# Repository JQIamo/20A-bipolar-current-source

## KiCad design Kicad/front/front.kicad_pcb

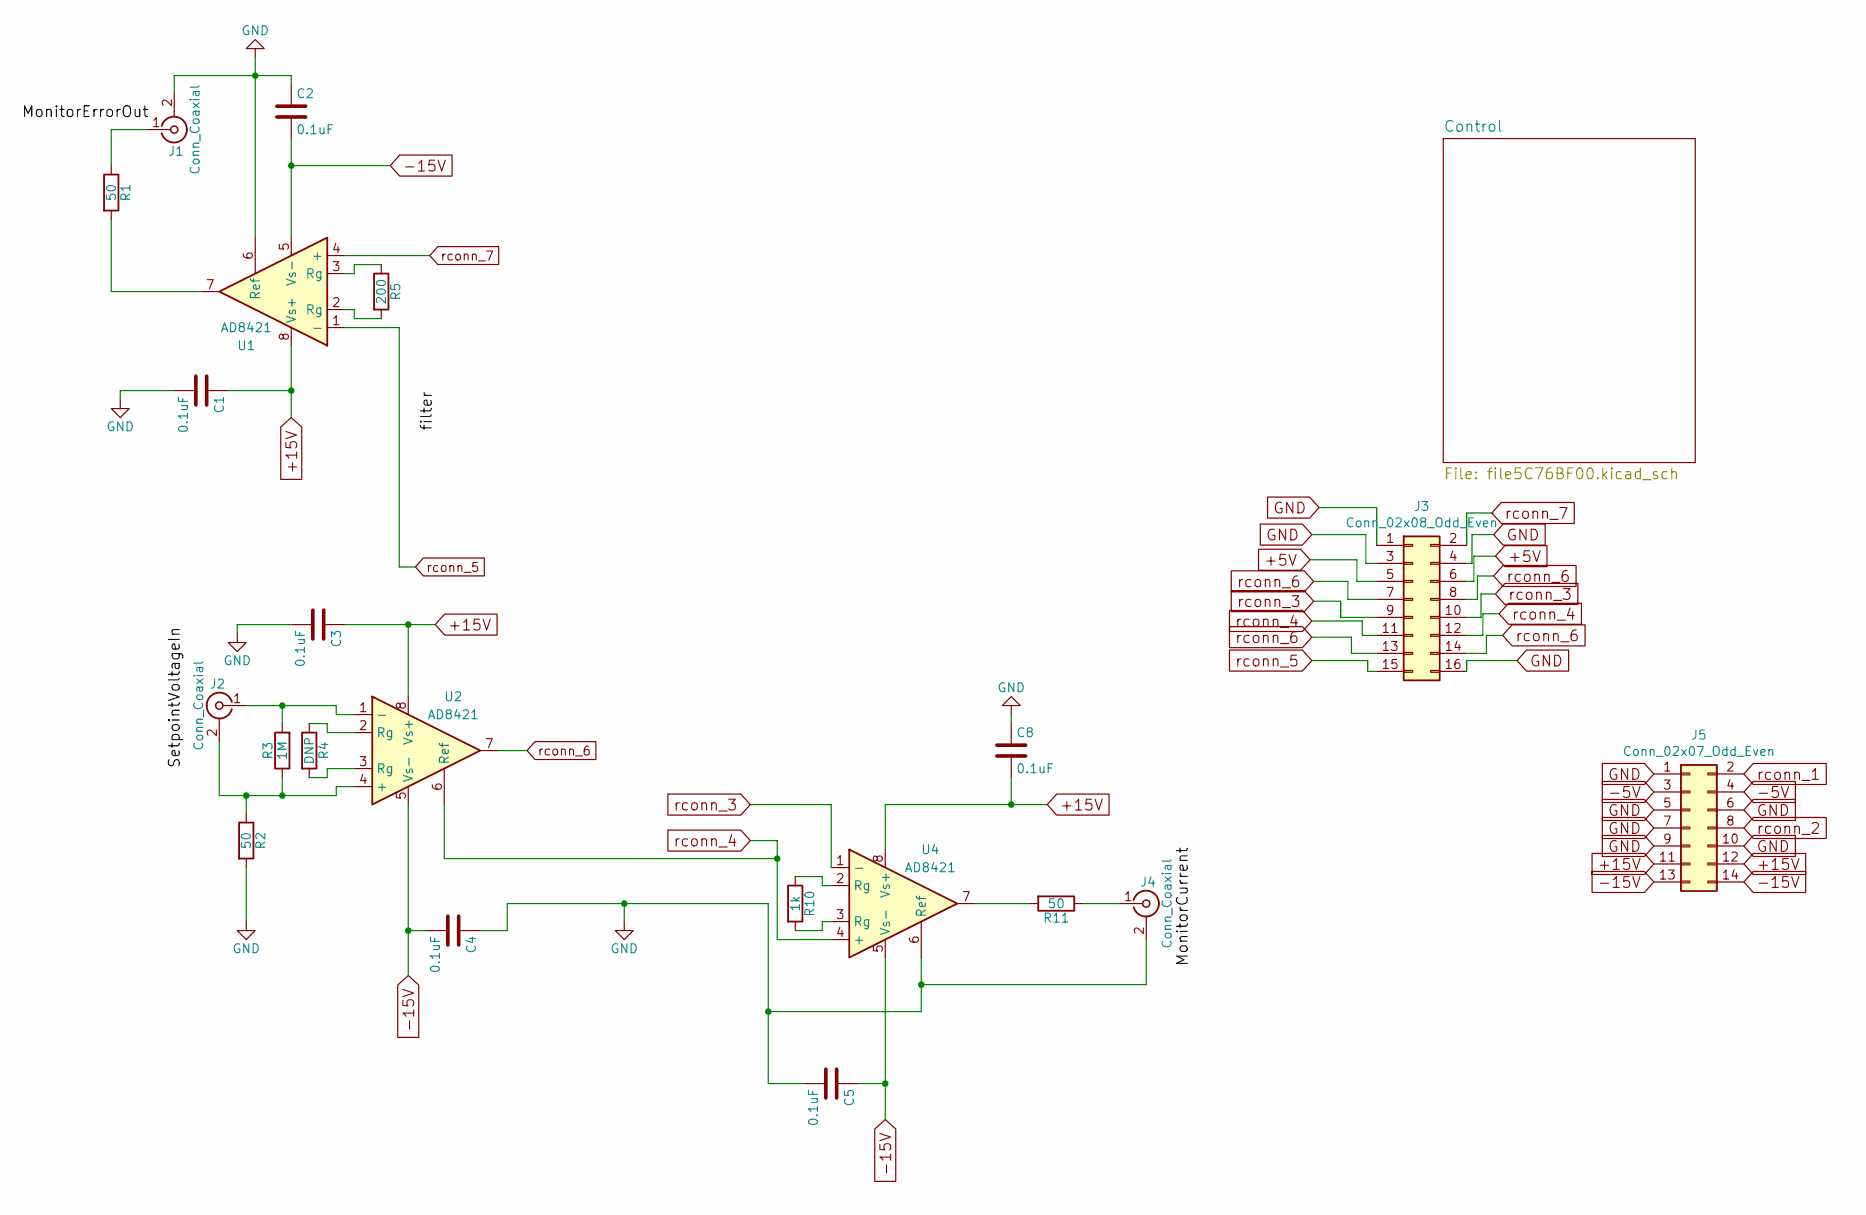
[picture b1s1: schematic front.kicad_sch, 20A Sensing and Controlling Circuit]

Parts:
C1, C2, C3, C4, C5, C8: 0.1uF; C_0603; MPN C0603C104J5RACAUTO; DIGIKEY PARTNO 399-6853-1-ND
J1, J2, J4: Conn_Coaxial; BNC-Vertical; MPN 5227222-3; DIGIKEY PARTNO A32262-ND
J3: Conn_02x08_Odd_Even; 16PinConn; DIGIKEY PARTNO ED10523-ND/ HHSC16H-ND
J5: Conn_02x07_Odd_Even; 14PinConn; DIGIKEY PARTNO ED10522-ND/ HHSC14H-ND
R1, R2, R11: 50; R_0603; MPN FC0603E50R0BTBST1; DIGIKEY PARTNO FC0603-50BFCT-ND
R3: 1M; R_0603; MPN MCT06030C1004FP500; DIGIKEY PARTNO MCT0603-1.00M-CFCT-ND
R4: DNP; R_0805
R5: 200; R_0603; MPN RNCF0603TKY200R; DIGIKEY PARTNO RNCF0603TKY200RCT-ND
R10: 1k; R_0603; MPN Y16291K00000T9R; DIGIKEY PARTNO Y1629-1.0KACT-ND
U1: AD8421; SOIC-8_3.9x4.9mm_Pitch1.27mm; MPN AD8421BRZ-R7; DIGIKEY PARTNO Value
U2, U4: AD8421; SOIC-8_3.9x4.9mm_Pitch1.27mm; MPN AD8421BRZ-R7; DIGIKEY PARTNO AD8421BRZ-R7CT-ND

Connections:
+5V: J3.5, J3.6; also elsewhere on the board
+15V: C1.1, C3.1, C8.2, J5.11, J5.12, U1.8 (Vs+), U2.8 (Vs+), U4.8 (Vs+); also elsewhere on the board
-5V: J5.3, J5.4; also elsewhere on the board
-15V: C2.2, C4.2, C5.1, J5.13, J5.14, U1.5 (Vs-), U2.5 (Vs-), U4.5 (Vs-); also elsewhere on the board
GND: C1.2, C2.1, C3.2, C4.1, C5.2, C8.1, J1.2 (Ext), J3.1, J3.3, J3.4, J3.16, J4.2 (Ext), J5.1, J5.5, J5.6, J5.7, J5.9, J5.10, R2.2, U1.6 (Ref), U4.6 (Ref); also elsewhere on the board
unnamed: J1.1 (In), R1.1
unnamed: J2.1 (In), R3.2, U2.1 (-)
unnamed: J2.2 (Ext), R2.1, R3.1, U2.4 (+)
unnamed: J4.1 (In), R11.1
unnamed: R1.2, U1.7
unnamed: R4.1, U2.2 (Rg)
unnamed: R4.2, U2.3 (Rg)
unnamed: R5.1, U1.3 (Rg)
unnamed: R5.2, U1.2 (Rg)
unnamed: R10.1, U4.2 (Rg)
unnamed: R10.2, U4.3 (Rg)
unnamed: R11.2, U4.7
rconn_1: J5.2; also elsewhere on the board
rconn_2: J5.8; also elsewhere on the board
rconn_3: J3.9, J3.10, U4.1 (-)
rconn_4: J3.11, J3.12, U2.6 (Ref), U4.4 (+)
rconn_5: J3.15, U1.1 (-)
rconn_6: J3.7, J3.8, J3.13, J3.14, U2.7
rconn_7: J3.2, U1.4 (+)

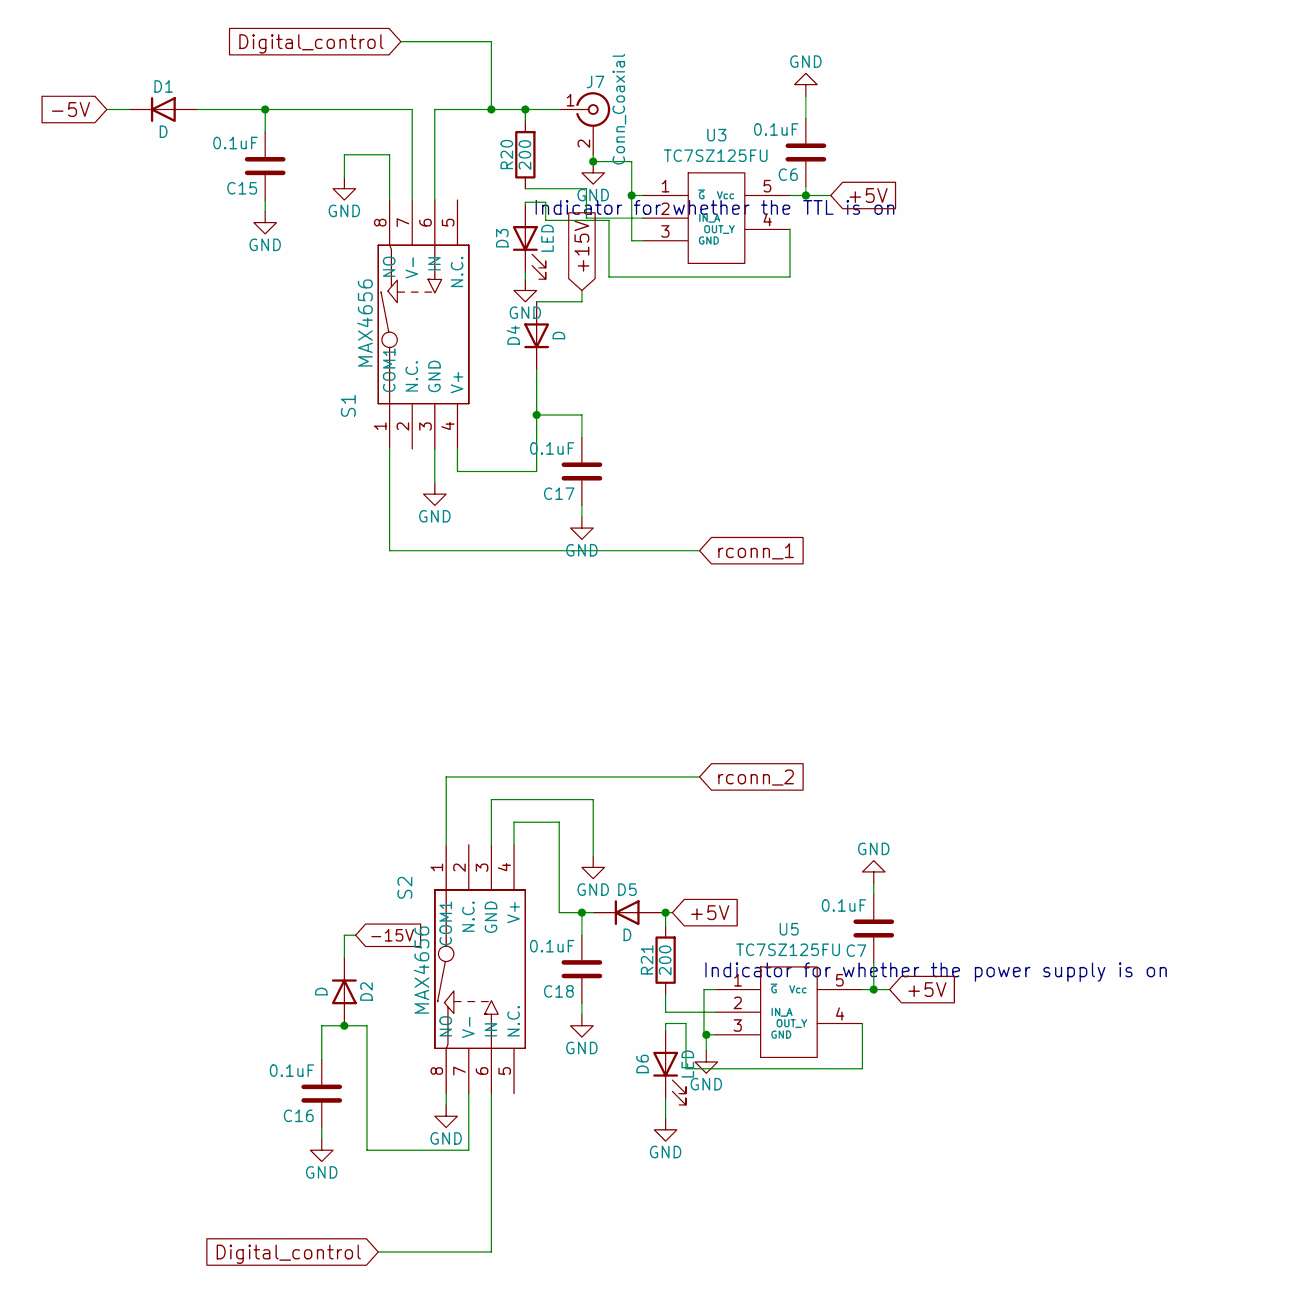
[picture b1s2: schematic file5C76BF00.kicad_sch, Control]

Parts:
C6, C7, C15, C16, C17, C18: 0.1uF; C_0603; MPN C0603C104J5RACAUTO; DIGIKEY PARTNO 399-6853-1-ND
D1, D2, D4, D5: D; Diode_SOD80; MPN CLL4150 TR; DIGIKEY PARTNO CLL4150CT-ND
D3, D6: LED; DIGIKEY PARTNO 516-2483-1-ND
J7: Conn_Coaxial; BNC-Vertical; MPN 5227222-3; DIGIKEY A32262-ND
R20, R21: 200; R_0805; MPN MCU08050C2201FP500; DIGIKEY 749-1728-1-ND
S1, S2: MAX4656; SOIC-8-1EP_3.9x4.9mm_Pitch1.27mm; DIGIKEY PARTNO MAX4656ESA+-ND
U3, U5: TC7SZ125FU; DIGIKEY PARTNO TC7SZ125FULJ(CTCT-ND

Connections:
+5V: C6.1, C7.1, D5.2 (A), R21.2, U3.5 (Vcc), U5.5 (Vcc); also elsewhere on the board
+15V: D4.2 (A); also elsewhere on the board
-5V: D1.1 (K); also elsewhere on the board
-15V: D2.1 (K); also elsewhere on the board
Digital_control: J7.1 (In), R20.2, S1.6 (IN), S2.6 (IN)
GND: C6.2, C7.2, C15.1, C16.1, C17.1, C18.1, D3.1 (K), D6.1 (K), J7.2 (Ext), S1.3 (GND), S1.8 (NO), S2.3 (GND), S2.8 (NO), U3.1 (~G), U3.3 (GND), U5.1 (~G), U5.3 (GND); also elsewhere on the board
unnamed: C15.2, D1.2 (A), S1.7 (V-)
unnamed: C16.2, D2.2 (A), S2.7 (V-)
unnamed: C17.2, D4.1 (K), S1.4 (V+)
unnamed: C18.2, D5.1 (K), S2.4 (V+)
unnamed: D3.2 (A), U3.4 (OUT_Y)
unnamed: D6.2 (A), U5.4 (OUT_Y)
unnamed: R20.1, U3.2 (IN_A)
unnamed: R21.1, U5.2 (IN_A)
rconn_1: S1.1 (COM1); also elsewhere on the board
rconn_2: S2.1 (COM1); also elsewhere on the board

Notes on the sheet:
Indicator for whether the TTL is on
Indicator for whether the power supply is on

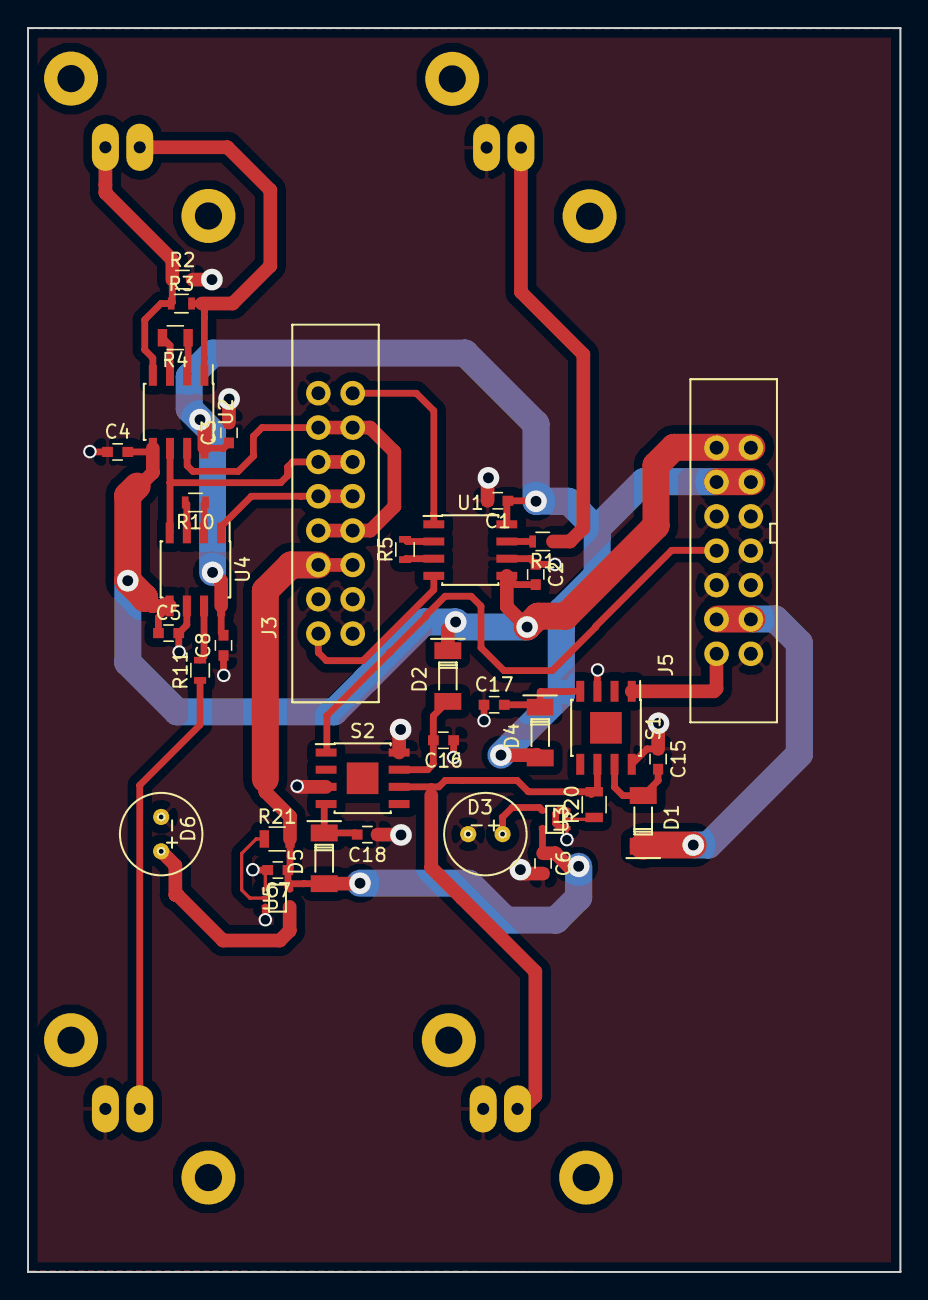
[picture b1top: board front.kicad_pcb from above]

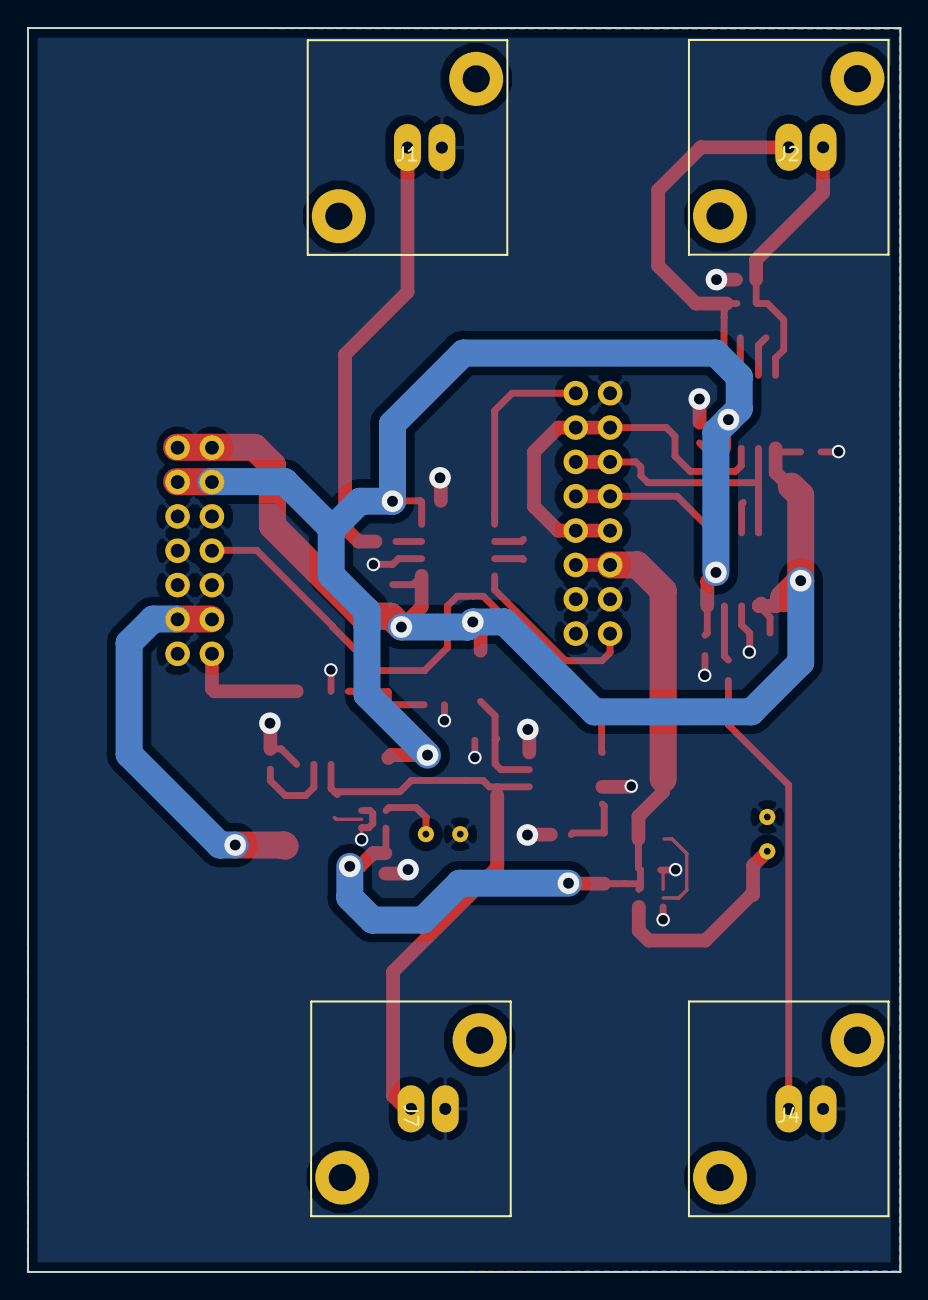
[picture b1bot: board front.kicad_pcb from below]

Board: 2 copper layers, 64.5 x 92.0 mm, 40 parts (4 on the bottom side), 33 nets.

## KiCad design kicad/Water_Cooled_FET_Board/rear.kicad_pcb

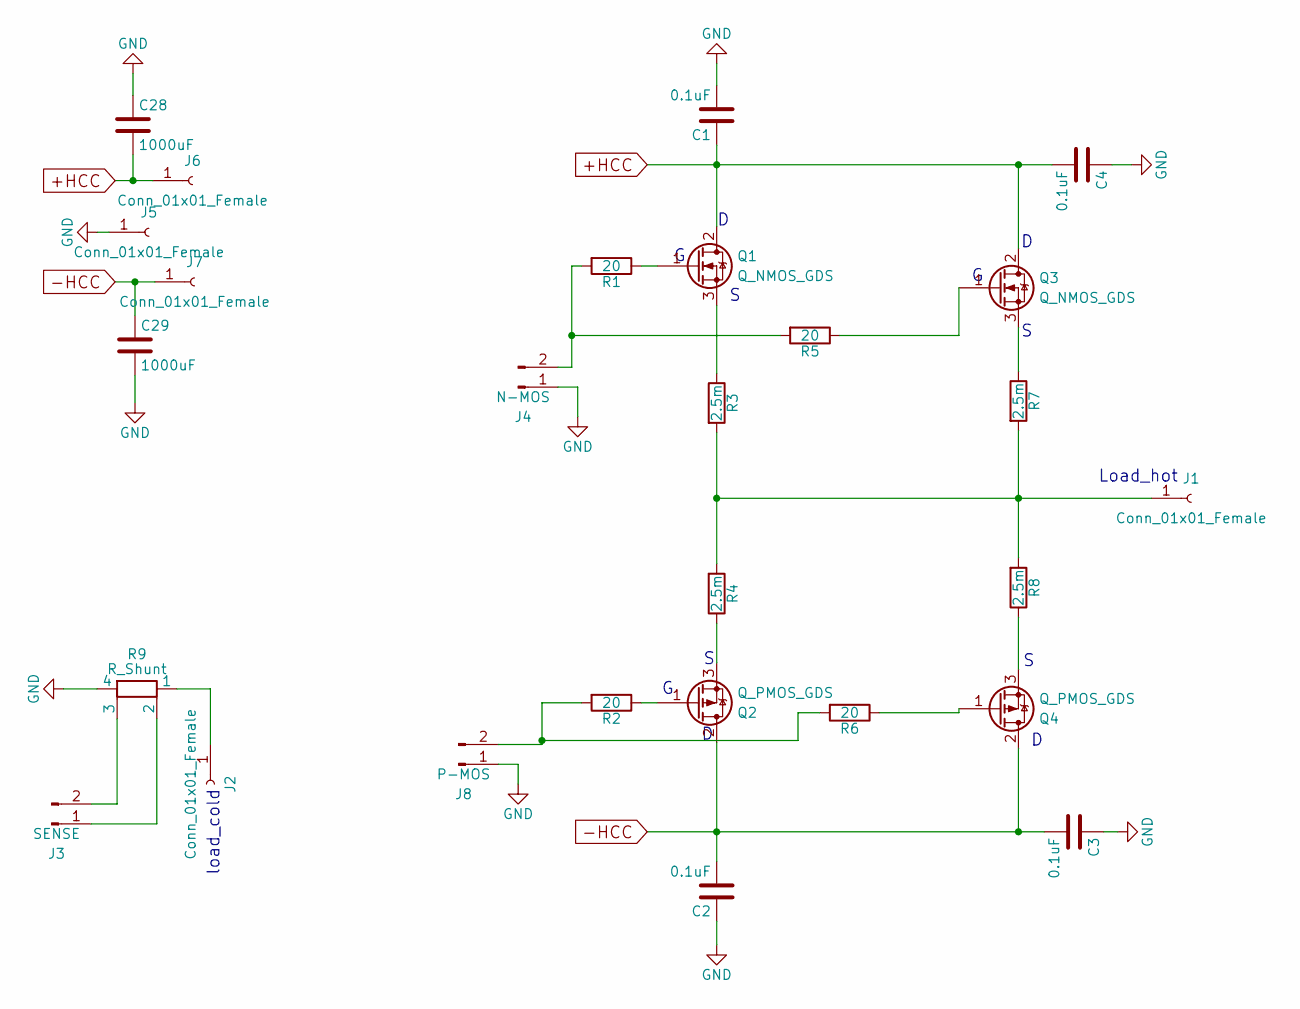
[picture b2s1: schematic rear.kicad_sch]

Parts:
C1, C2, C3, C4: 0.1uF; C_0603; MPN C0603C104J5RACAUTO; DIGIKEY PARTNO 399-6853-1-ND
C28, C29: 1000uF; CAPCITOR_TOT; DIGIKEY PARTNO 647-UKL1J102KHD
J1, J2, J5, J6, J7: Conn_01x01_Female; SAFETY-BANANA-JACK-CT3151
J3: SENSE; PinHeader_1x02_P2.54mm_Vertical
J4: N-MOS; PinHeader_1x02_P2.54mm_Vertical
J8: P-MOS; PinHeader_1x02_P2.54mm_Vertical
Q1, Q3: Q_NMOS_GDS; PowerMOS; DIGIKEY PARTNO IXFN520N075T2-ND
Q2, Q4: Q_PMOS_GDS; PowerMOS; DIGIKEY PARTNO IXTN170P10P-ND
R1, R2, R5, R6: 20; R_0603_1608Metric_Pad0.98x0.95mm_HandSolder; DIGIKEY PARTNO P20.00BYCT-ND
R3, R4, R7, R8: 2.5m; R_2512; DIGIKEY PARTNO A129569CT-ND
R9: R_Shunt; SHR4-3825

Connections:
+HCC: C1.1, C4.2, C28.2, J6.1, Q1.2 (D), Q3.2 (D)
-HCC: C2.2, C3.2, C29.1, J7.1, Q2.2 (D), Q4.2 (D)
GND: C1.2, C2.1, C3.1, C4.1, C28.1, C29.2, J4.1, J5.1, J8.1, R9.4
unnamed: J1.1, R3.2, R4.2, R7.2, R8.2
unnamed: J2.1, R9.1
unnamed: J3.1, R9.2
unnamed: J3.2, R9.3
unnamed: J4.2, R1.2, R5.2
unnamed: J8.2, R2.2, R6.2
unnamed: Q1.1 (G), R1.1
unnamed: Q1.3 (S), R3.1
unnamed: Q2.1 (G), R2.1
unnamed: Q2.3 (S), R4.1
unnamed: Q3.1 (G), R5.1
unnamed: Q3.3 (S), R7.1
unnamed: Q4.1 (G), R6.1
unnamed: Q4.3 (S), R8.1

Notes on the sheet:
load_cold
Load_hot

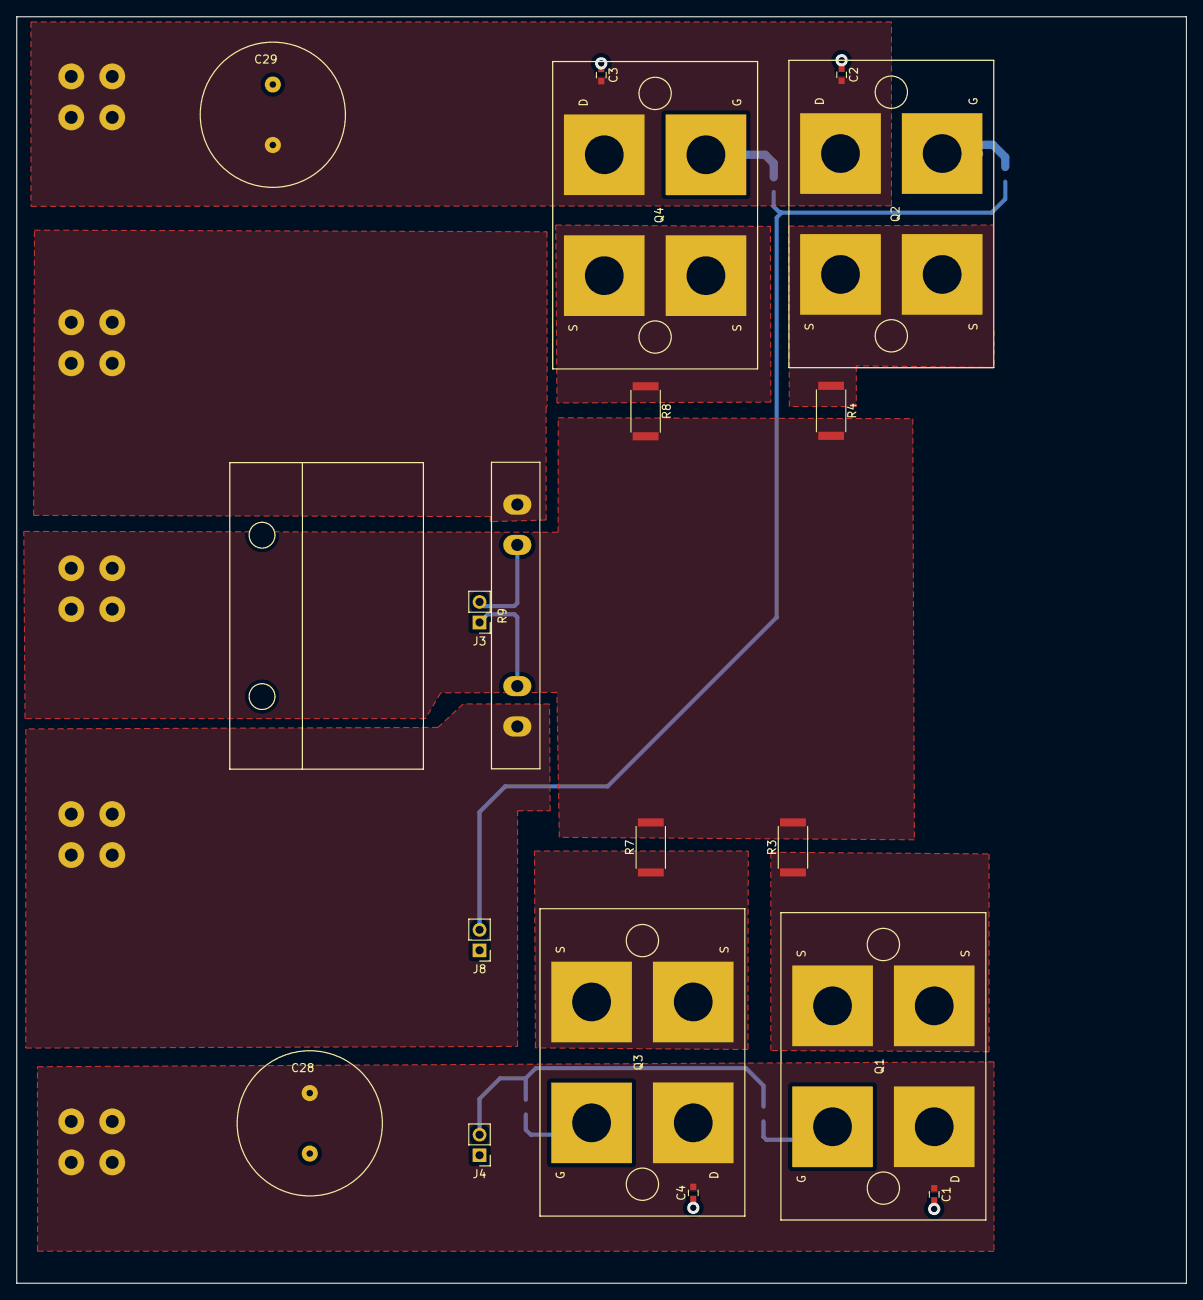
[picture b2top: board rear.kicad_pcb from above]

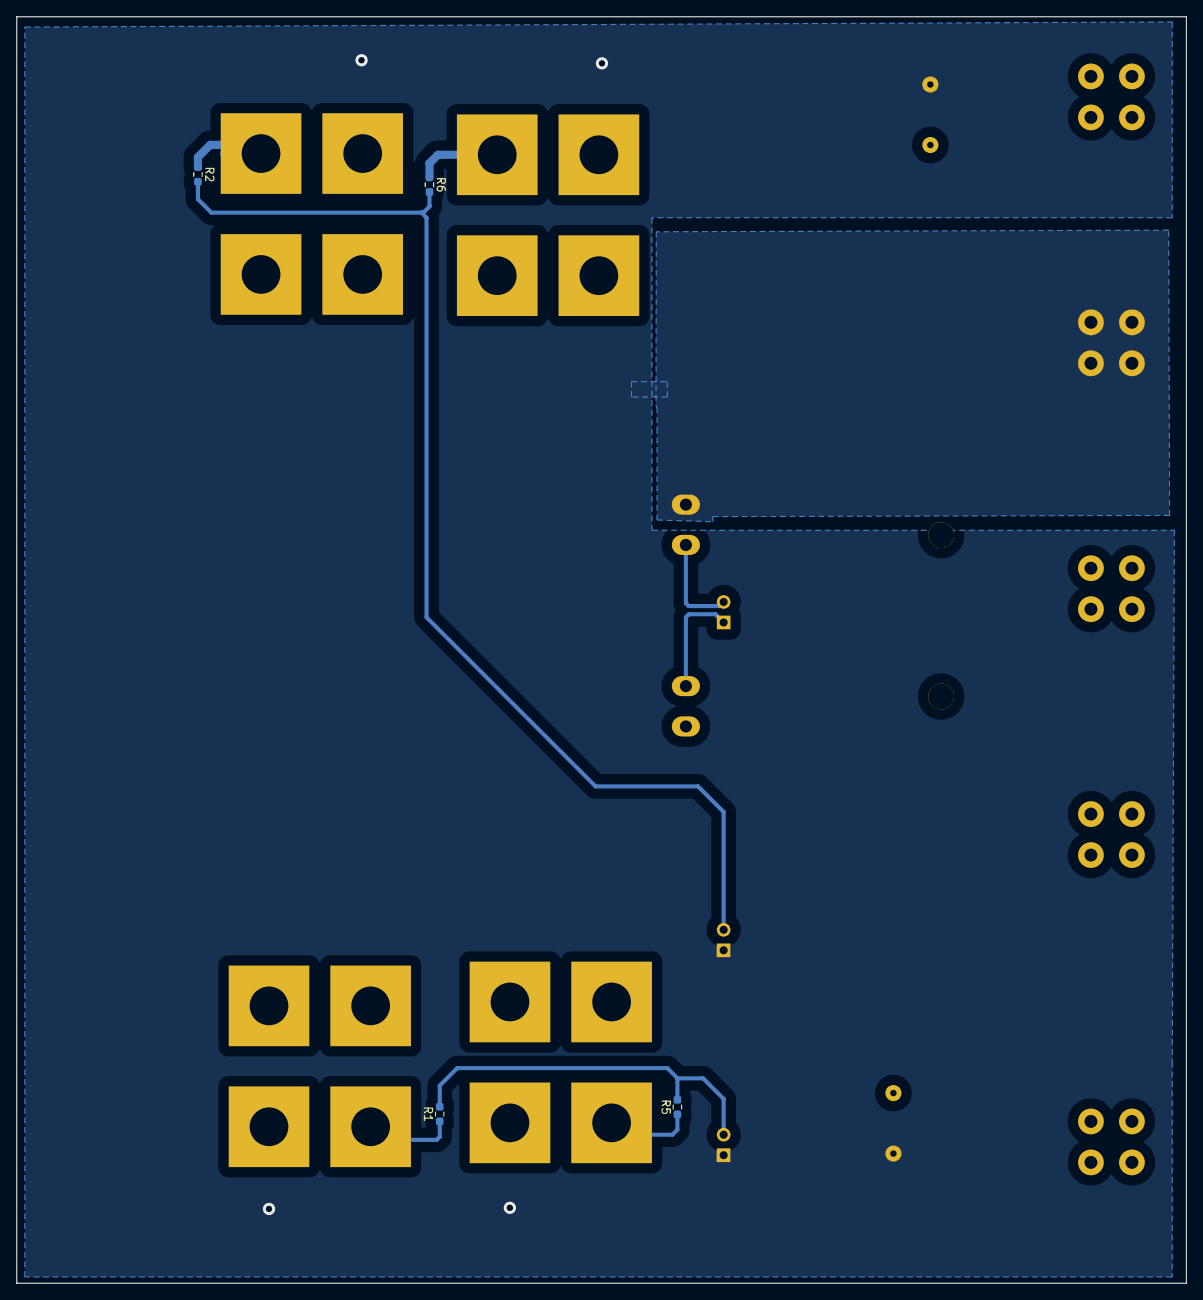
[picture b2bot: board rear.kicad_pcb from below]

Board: 2 copper layers, 145.0 x 157.0 mm, 27 parts (4 on the bottom side), 17 nets.
